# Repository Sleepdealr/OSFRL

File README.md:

# OSFRL

FRL PCB made with STM32F072 and Molex EZMate

Source PCB files provided in the `PCB/` folder, with firmware source in the `Firmware/` folder

These have been tested and are working

<br />This work is licensed under a <a rel="license" href="http://creativecommons.org/licenses/by-nc-sa/4.0/">Creative Commons Attribution-NonCommercial-ShareAlike 4.0 Unported License</a>.

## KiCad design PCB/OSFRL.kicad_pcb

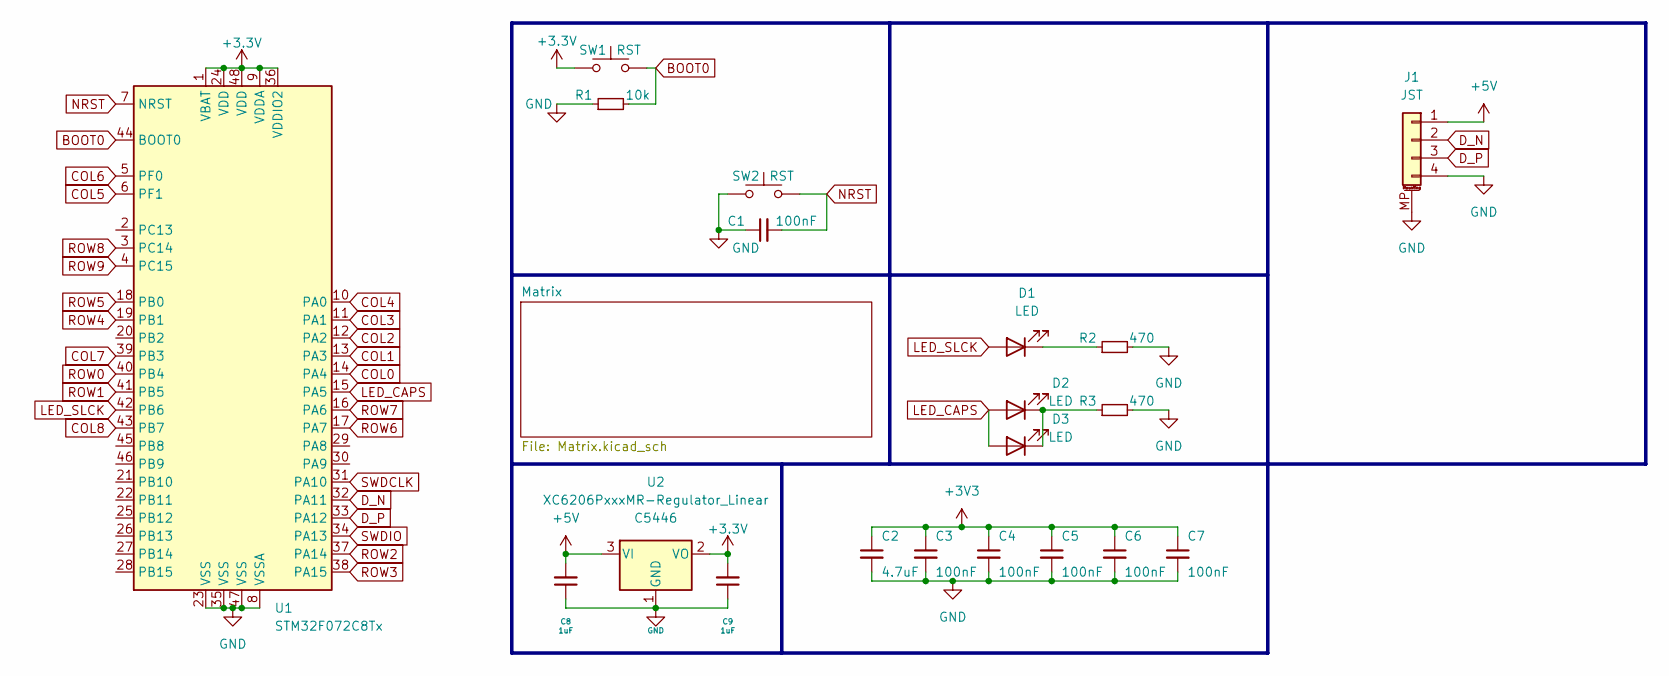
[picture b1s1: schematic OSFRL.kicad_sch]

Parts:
C1, C3, C4, C5, C6, C7: 100nF; C_0402_1005Metric; LCSC C307331
C2: 4.7uF; C_0402_1005Metric; LCSC C52923
C8, C9: 1uF; C_0402_1005Metric; LCSC C52923
D1, D2: LED; LED_MX_3mm
D3: LED; LED_MX_3mm-FLIPPED
J1: JST; MOLEX_781710004_MountingReliefs; LCSC C145956
R1: 10k; R_0402_1005Metric
R2, R3: 470; R_0402_1005Metric
SW1, SW2: RST; SW_SPST_SKQG_WithoutStem
U1: STM32F072C8Tx; LQFP-48_7x7mm_P0.5mm
U2: XC6206PxxxMR-Regulator_Linear; SOT-23; LCSC C5446

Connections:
+5V: C8.2, J1.1, U2.3 (VI)
BOOT0: R1.2, SW1.2, U1.44 (BOOT0)
COL0: U1.14 (PA4); also elsewhere on the board
COL1: U1.13 (PA3); also elsewhere on the board
COL2: U1.12 (PA2); also elsewhere on the board
COL3: U1.11 (PA1); also elsewhere on the board
COL4: U1.10 (PA0); also elsewhere on the board
COL5: U1.6 (PF1); also elsewhere on the board
COL6: U1.5 (PF0); also elsewhere on the board
COL7: U1.39 (PB3); also elsewhere on the board
COL8: U1.43 (PB7); also elsewhere on the board
D_N: J1.2, U1.32 (PA11)
D_P: J1.3, U1.33 (PA12)
GND: C1.1, C2.2, C3.2, C4.2, C5.2, C6.2, C7.2, C8.1, C9.1, J1.4, J1.MP (MountPin), R1.1, R2.2, R3.2, SW2.1, U1.8 (VSSA), U1.23 (VSS), U1.35 (VSS), U1.47 (VSS), U2.1 (GND)
LED_CAPS: D2.2 (A), D3.2 (A), U1.15 (PA5)
LED_SLCK: D1.2 (A), U1.42 (PB6)
NRST: C1.2, SW2.2, U1.7 (NRST)
unnamed: D1.1 (K), R2.1
unnamed: D2.1 (K), D3.1 (K), R3.1
ROW0: U1.40 (PB4); also elsewhere on the board
ROW1: U1.41 (PB5); also elsewhere on the board
ROW2: U1.37 (PA14); also elsewhere on the board
ROW3: U1.38 (PA15); also elsewhere on the board
ROW4: U1.19 (PB1); also elsewhere on the board
ROW5: U1.18 (PB0); also elsewhere on the board
ROW6: U1.17 (PA7); also elsewhere on the board
ROW7: U1.16 (PA6); also elsewhere on the board
ROW8: U1.3 (PC14); also elsewhere on the board
ROW9: U1.4 (PC15); also elsewhere on the board
SWDCLK: U1.31 (PA10)
SWDIO: U1.34 (PA13)

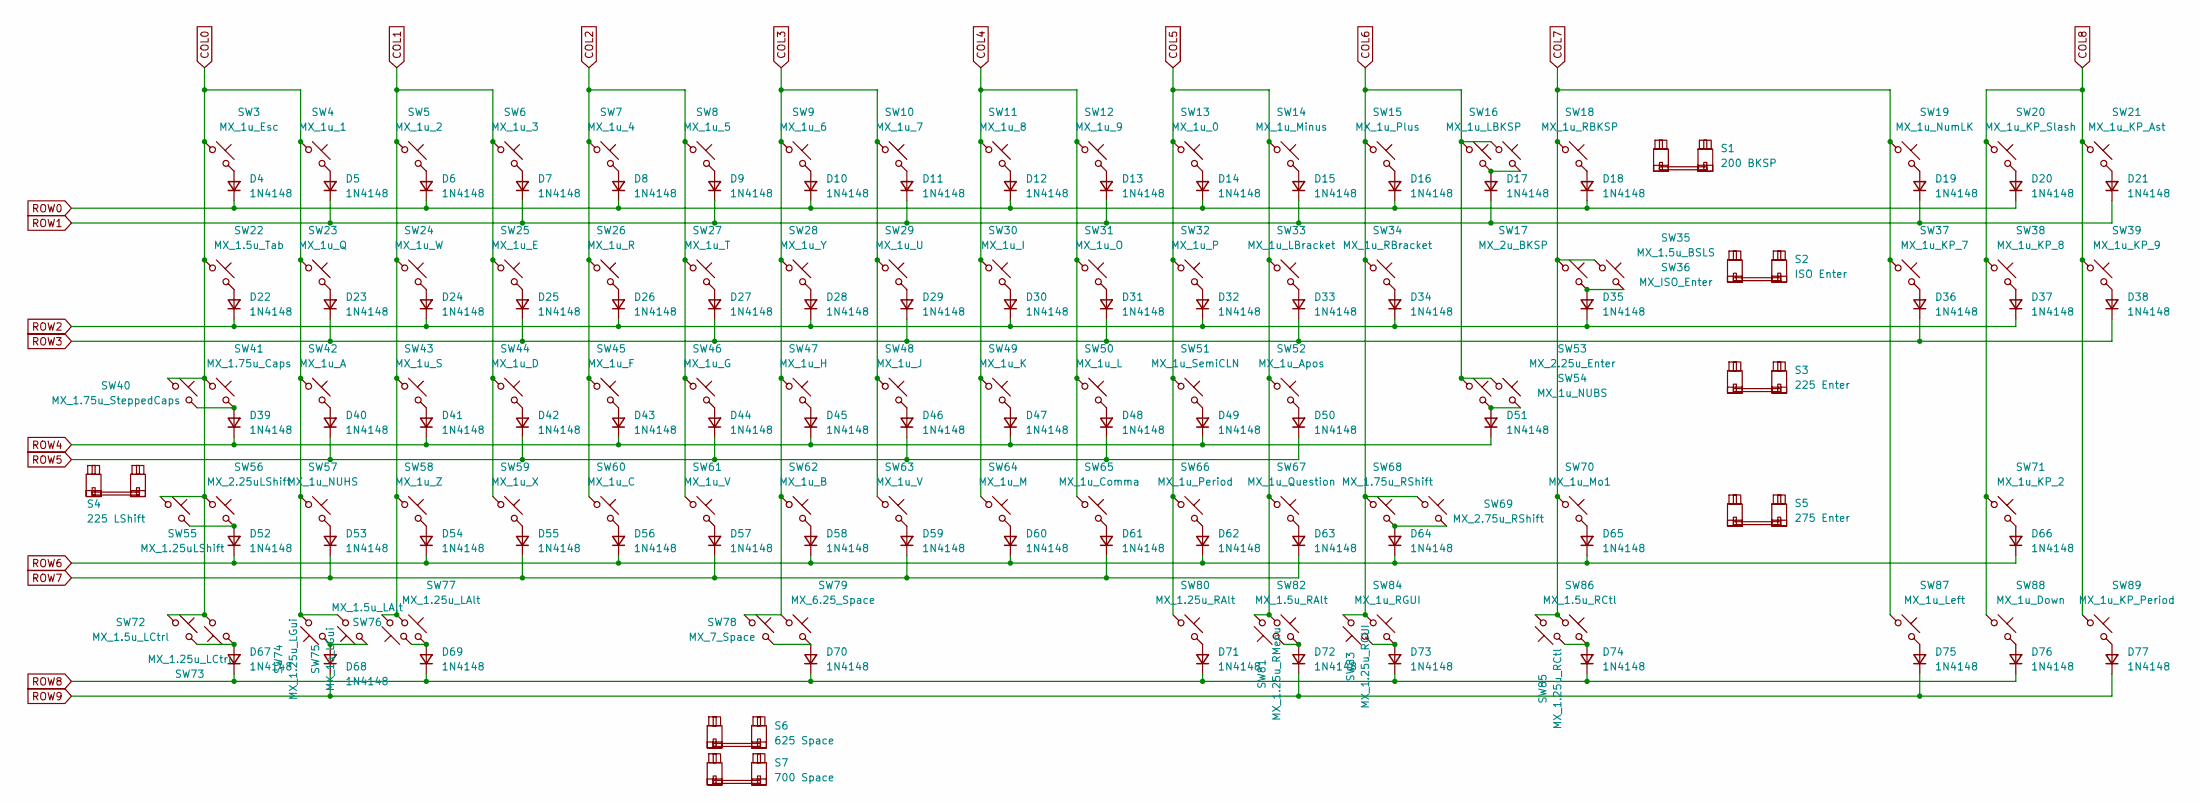
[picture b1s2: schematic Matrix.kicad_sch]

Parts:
D4, D5, D6, D7, D8, D9, D10, D11, D12, D13, D14, D15, D16, D17, D18, D19, D20, D21, D22, D23, D24, D25, D26, D27, D28, D29, D30, D31, D32, D33, D34, D35, D36, D37, D38, D39, D40, D41, D42, D43, D44, D45, D46, D47, D48, D49, D50, D51, D52, D53, D54, D55, D56, D57, D58, D59, D60, D61, D62, D63, D64, D65, D66, D67, D68, D69, D70, D71, D72, D73, D74, D75, D76, D77: 1N4148; D_SOD-123-EditSkilk
S1: 200 BKSP; STAB_MX_P_2u
S2: ISO Enter; STAB_MX_P_ISO_FLIPPED
S3: 225 Enter; STAB_MX_P_2.25u
S4: 225 LShift; STAB_MX_P_2.25u
S5: 275 Enter; STAB_MX_P_2.75u
S6: 625 Space; STAB_MX_P_6.25u
S7: 700 Space; STAB_MX_P_7u
SW3: MX_1u_Esc; SW_MX_1u
SW4: MX_1u_1; SW_MX_1u
SW5: MX_1u_2; SW_MX_1u
SW6: MX_1u_3; SW_MX_1u
SW7: MX_1u_4; SW_MX_1u
SW8: MX_1u_5; SW_MX_1u
SW9: MX_1u_6; SW_MX_1u
SW10: MX_1u_7; SW_MX_1u
SW11: MX_1u_8; SW_MX_1u
SW12: MX_1u_9; SW_MX_1u
SW13: MX_1u_0; SW_MX_1u
SW14: MX_1u_Minus; SW_MX_1u
SW15: MX_1u_Plus; SW_MX_1u
SW16: MX_1u_LBKSP; SW_MX_1u
SW17: MX_2u_BKSP; SW_MX_1u
SW18: MX_1u_RBKSP; SW_MX_1u
SW19: MX_1u_NumLK; SW_MX_1u
SW20: MX_1u_KP_Slash; SW_MX_1u
SW21: MX_1u_KP_Ast; SW_MX_1u
SW22: MX_1.5u_Tab; SW_MX_1.5u
SW23: MX_1u_Q; SW_MX_1u
SW24: MX_1u_W; SW_MX_1u
SW25: MX_1u_E; SW_MX_1u
SW26: MX_1u_R; SW_MX_1u
SW27: MX_1u_T; SW_MX_1u
SW28: MX_1u_Y; SW_MX_1u
SW29: MX_1u_U; SW_MX_1u
SW30: MX_1u_I; SW_MX_1u
SW31: MX_1u_O; SW_MX_1u
SW32: MX_1u_P; SW_MX_1u
SW33: MX_1u_LBracket; SW_MX_1u
SW34: MX_1u_RBracket; SW_MX_1u
SW35: MX_1.5u_BSLS; SW_MX_1.5u
SW36: MX_ISO_Enter; SW_MX_1u
SW37: MX_1u_KP_7; SW_MX_1u
SW38: MX_1u_KP_8; SW_MX_1u
SW39: MX_1u_KP_9; SW_MX_1u
SW40: MX_1.75u_SteppedCaps; SW_MX_1.75u_stp
SW41: MX_1.75u_Caps; SW_MX_1.75u
SW42: MX_1u_A; SW_MX_1u
SW43: MX_1u_S; SW_MX_1u
SW44: MX_1u_D; SW_MX_1u
SW45: MX_1u_F; SW_MX_1u
SW46: MX_1u_G; SW_MX_1u
SW47: MX_1u_H; SW_MX_1u
SW48: MX_1u_J; SW_MX_1u
SW49: MX_1u_K; SW_MX_1u
SW50: MX_1u_L; SW_MX_1u
SW51: MX_1u_SemiCLN; SW_MX_1u
SW52: MX_1u_Apos; SW_MX_1u
SW53: MX_2.25u_Enter; SW_MX_1u
SW54: MX_1u_NUBS; SW_MX_1u
SW55: MX_1.25uLShift; SW_MX_1.25u
SW56: MX_2.25uLShift; SW_MX_1u
SW57: MX_1u_NUHS; SW_MX_1u
SW58: MX_1u_Z; SW_MX_1u
SW59: MX_1u_X; SW_MX_1u
SW60: MX_1u_C; SW_MX_1u
SW61, SW63: MX_1u_V; SW_MX_1u
SW62: MX_1u_B; SW_MX_1u
SW64: MX_1u_M; SW_MX_1u
SW65: MX_1u_Comma; SW_MX_1u
SW66: MX_1u_Period; SW_MX_1u
SW67: MX_1u_Question; SW_MX_1u
SW68: MX_1.75u_RShift; SW_MX_1.75u
SW69: MX_2.75u_RShift; SW_MX_1u
SW70: MX_1u_Mo1; SW_MX_1u
SW71: MX_1u_KP_2; SW_MX_1u
SW72: MX_1.5u_LCtrl; SW_MX_1.5u
SW73: MX_1.25u_LCtrl; SW_MX_1.25u
SW74: MX_1.25u_LGui; SW_MX_1.25u
SW75: MX_1u_LGui; SW_MX_1u
SW76: MX_1.5u_LAlt; SW_MX_1.5u
SW77: MX_1.25u_LAlt; SW_MX_1.25u
SW78: MX_7_Space; SW_MX_1u
SW79: MX_6.25_Space; SW_MX_1u
SW80: MX_1.25u_RAlt; SW_MX_1.25u
SW81: MX_1.25u_RMenu; SW_MX_1.25u
SW82: MX_1.5u_RAlt; SW_MX_1.5u
SW83: MX_1.25u_RGUI; SW_MX_1.25u
SW84: MX_1u_RGUI; SW_MX_1u
SW85: MX_1.25u_RCtl; SW_MX_1.25u
SW86: MX_1.5u_RCtl; SW_MX_1.5u
SW87: MX_1u_Left; SW_MX_1u
SW88: MX_1u_Down; SW_MX_1u
SW89: MX_1u_KP_Period; SW_MX_1u

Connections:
COL0: SW3.1, SW4.1, SW22.1, SW23.1, SW40.1, SW41.1, SW42.1, SW55.1, SW56.1, SW57.1, SW72.1, SW73.1, SW74.1, SW75.1; also elsewhere on the board
COL1: SW5.1, SW6.1, SW24.1, SW25.1, SW43.1, SW44.1, SW58.1, SW59.1, SW76.1, SW77.1; also elsewhere on the board
COL2: SW7.1, SW8.1, SW26.1, SW27.1, SW45.1, SW46.1, SW60.1, SW61.1; also elsewhere on the board
COL3: SW9.1, SW10.1, SW28.1, SW29.1, SW47.1, SW48.1, SW62.1, SW63.1, SW78.1, SW79.1; also elsewhere on the board
COL4: SW11.1, SW12.1, SW30.1, SW31.1, SW49.1, SW50.1, SW64.1, SW65.1; also elsewhere on the board
COL5: SW13.1, SW14.1, SW32.1, SW33.1, SW51.1, SW52.1, SW66.1, SW67.1, SW80.1, SW81.1, SW82.1; also elsewhere on the board
COL6: SW15.1, SW16.1, SW17.1, SW34.1, SW53.1, SW54.1, SW68.1, SW69.1, SW83.1, SW84.1; also elsewhere on the board
COL7: SW18.1, SW19.1, SW35.1, SW36.1, SW37.1, SW70.1, SW85.1, SW86.1, SW87.1; also elsewhere on the board
COL8: SW20.1, SW21.1, SW38.1, SW39.1, SW71.1, SW88.1, SW89.1; also elsewhere on the board
unnamed: D4.2 (A), SW3.2
unnamed: D5.2 (A), SW4.2
unnamed: D6.2 (A), SW5.2
unnamed: D7.2 (A), SW6.2
unnamed: D8.2 (A), SW7.2
unnamed: D9.2 (A), SW8.2
unnamed: D10.2 (A), SW9.2
unnamed: D11.2 (A), SW10.2
unnamed: D12.2 (A), SW11.2
unnamed: D13.2 (A), SW12.2
unnamed: D14.2 (A), SW13.2
unnamed: D15.2 (A), SW14.2
unnamed: D16.2 (A), SW15.2
unnamed: D17.2 (A), SW16.2, SW17.2
unnamed: D18.2 (A), SW18.2
unnamed: D19.2 (A), SW19.2
unnamed: D20.2 (A), SW20.2
unnamed: D21.2 (A), SW21.2
unnamed: D22.2 (A), SW22.2
unnamed: D23.2 (A), SW23.2
unnamed: D24.2 (A), SW24.2
unnamed: D25.2 (A), SW25.2
unnamed: D26.2 (A), SW26.2
unnamed: D27.2 (A), SW27.2
unnamed: D28.2 (A), SW28.2
unnamed: D29.2 (A), SW29.2
unnamed: D30.2 (A), SW30.2
unnamed: D31.2 (A), SW31.2
unnamed: D32.2 (A), SW32.2
unnamed: D33.2 (A), SW33.2
unnamed: D34.2 (A), SW34.2
unnamed: D35.2 (A), SW35.2, SW36.2
unnamed: D36.2 (A), SW37.2
unnamed: D37.2 (A), SW38.2
unnamed: D38.2 (A), SW39.2
unnamed: D39.2 (A), SW40.2, SW41.2
unnamed: D40.2 (A), SW42.2
unnamed: D41.2 (A), SW43.2
unnamed: D42.2 (A), SW44.2
unnamed: D43.2 (A), SW45.2
unnamed: D44.2 (A), SW46.2
unnamed: D45.2 (A), SW47.2
unnamed: D46.2 (A), SW48.2
unnamed: D47.2 (A), SW49.2
unnamed: D48.2 (A), SW50.2
unnamed: D49.2 (A), SW51.2
unnamed: D50.2 (A), SW52.2
unnamed: D51.2 (A), SW53.2, SW54.2
unnamed: D52.2 (A), SW55.2, SW56.2
unnamed: D53.2 (A), SW57.2
unnamed: D54.2 (A), SW58.2
unnamed: D55.2 (A), SW59.2
unnamed: D56.2 (A), SW60.2
unnamed: D57.2 (A), SW61.2
unnamed: D58.2 (A), SW62.2
unnamed: D59.2 (A), SW63.2
unnamed: D60.2 (A), SW64.2
unnamed: D61.2 (A), SW65.2
unnamed: D62.2 (A), SW66.2
unnamed: D63.2 (A), SW67.2
unnamed: D64.2 (A), SW68.2, SW69.2
unnamed: D65.2 (A), SW70.2
unnamed: D66.2 (A), SW71.2
unnamed: D67.2 (A), SW72.2, SW73.2
unnamed: D68.2 (A), SW74.2, SW75.2
unnamed: D69.2 (A), SW76.2, SW77.2
unnamed: D70.2 (A), SW78.2, SW79.2
unnamed: D71.2 (A), SW80.2
unnamed: D72.2 (A), SW81.2, SW82.2
unnamed: D73.2 (A), SW83.2, SW84.2
unnamed: D74.2 (A), SW85.2, SW86.2
unnamed: D75.2 (A), SW87.2
unnamed: D76.2 (A), SW88.2
unnamed: D77.2 (A), SW89.2
ROW0: D4.1 (K), D6.1 (K), D8.1 (K), D10.1 (K), D12.1 (K), D14.1 (K), D16.1 (K), D18.1 (K), D20.1 (K); also elsewhere on the board
ROW1: D5.1 (K), D7.1 (K), D9.1 (K), D11.1 (K), D13.1 (K), D15.1 (K), D17.1 (K), D19.1 (K), D21.1 (K); also elsewhere on the board
ROW2: D22.1 (K), D24.1 (K), D26.1 (K), D28.1 (K), D30.1 (K), D32.1 (K), D34.1 (K), D35.1 (K), D37.1 (K); also elsewhere on the board
ROW3: D23.1 (K), D25.1 (K), D27.1 (K), D29.1 (K), D31.1 (K), D33.1 (K), D36.1 (K), D38.1 (K); also elsewhere on the board
ROW4: D39.1 (K), D41.1 (K), D43.1 (K), D45.1 (K), D47.1 (K), D49.1 (K), D51.1 (K); also elsewhere on the board
ROW5: D40.1 (K), D42.1 (K), D44.1 (K), D46.1 (K), D48.1 (K), D50.1 (K); also elsewhere on the board
ROW6: D52.1 (K), D54.1 (K), D56.1 (K), D58.1 (K), D60.1 (K), D62.1 (K), D64.1 (K), D65.1 (K), D66.1 (K); also elsewhere on the board
ROW7: D53.1 (K), D55.1 (K), D57.1 (K), D59.1 (K), D61.1 (K), D63.1 (K); also elsewhere on the board
ROW8: D67.1 (K), D69.1 (K), D70.1 (K), D71.1 (K), D73.1 (K), D74.1 (K), D76.1 (K); also elsewhere on the board
ROW9: D68.1 (K), D72.1 (K), D75.1 (K), D77.1 (K); also elsewhere on the board

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
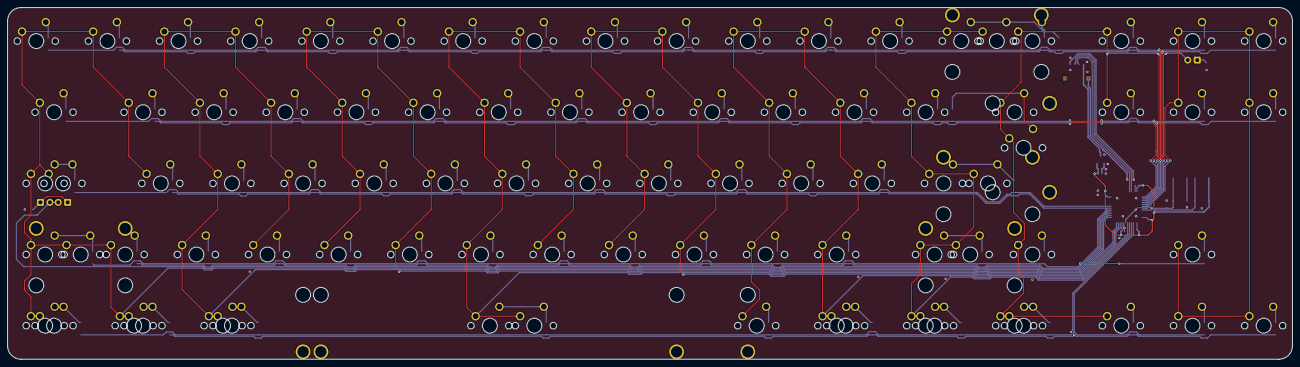
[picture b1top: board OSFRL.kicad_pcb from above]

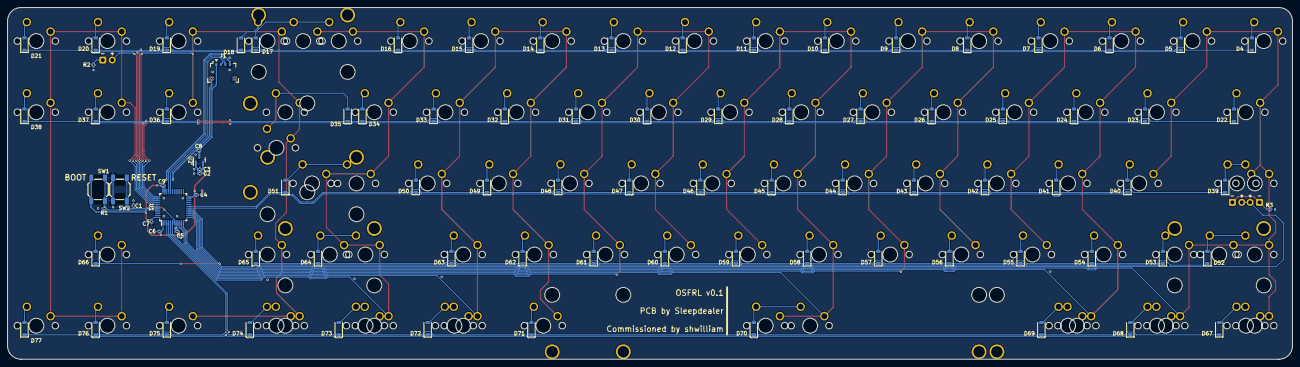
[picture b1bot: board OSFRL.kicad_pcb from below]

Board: 2 copper layers, 344.0 x 94.1 mm, 188 parts (91 on the bottom side), 104 nets.

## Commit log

2023-02-13 init to winit
2023-02-19 Add license
